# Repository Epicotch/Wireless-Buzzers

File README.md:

# Wireless Buzzers

### **NOTE: This thing was fairly slapdash and still has a few bugs. Only use this as a reference, not as a final product.**

3D printed parts: https://cad.onshape.com/documents/be3b52bcdf6f61d23120cde6/w/8980feb9664c58ae24ebe7fa/e/dfef3d1a1d06f241238ca187?renderMode=0&uiState=6670e02500c0bf5a21c60121

Shield: [![CC BY-NC 4.0][cc-by-nc-shield]][cc-by-nc]

This work is licensed under a
[Creative Commons Attribution-NonCommercial 4.0 International License][cc-by-nc].

[![CC BY-NC 4.0][cc-by-nc-image]][cc-by-nc]

[cc-by-nc]: https://creativecommons.org/licenses/by-nc/4.0/
[cc-by-nc-image]: https://licensebuttons.net/l/by-nc/4.0/88x31.png
[cc-by-nc-shield]: https://img.shields.io/badge/License-CC%20BY--NC%204.0-lightgrey.svg

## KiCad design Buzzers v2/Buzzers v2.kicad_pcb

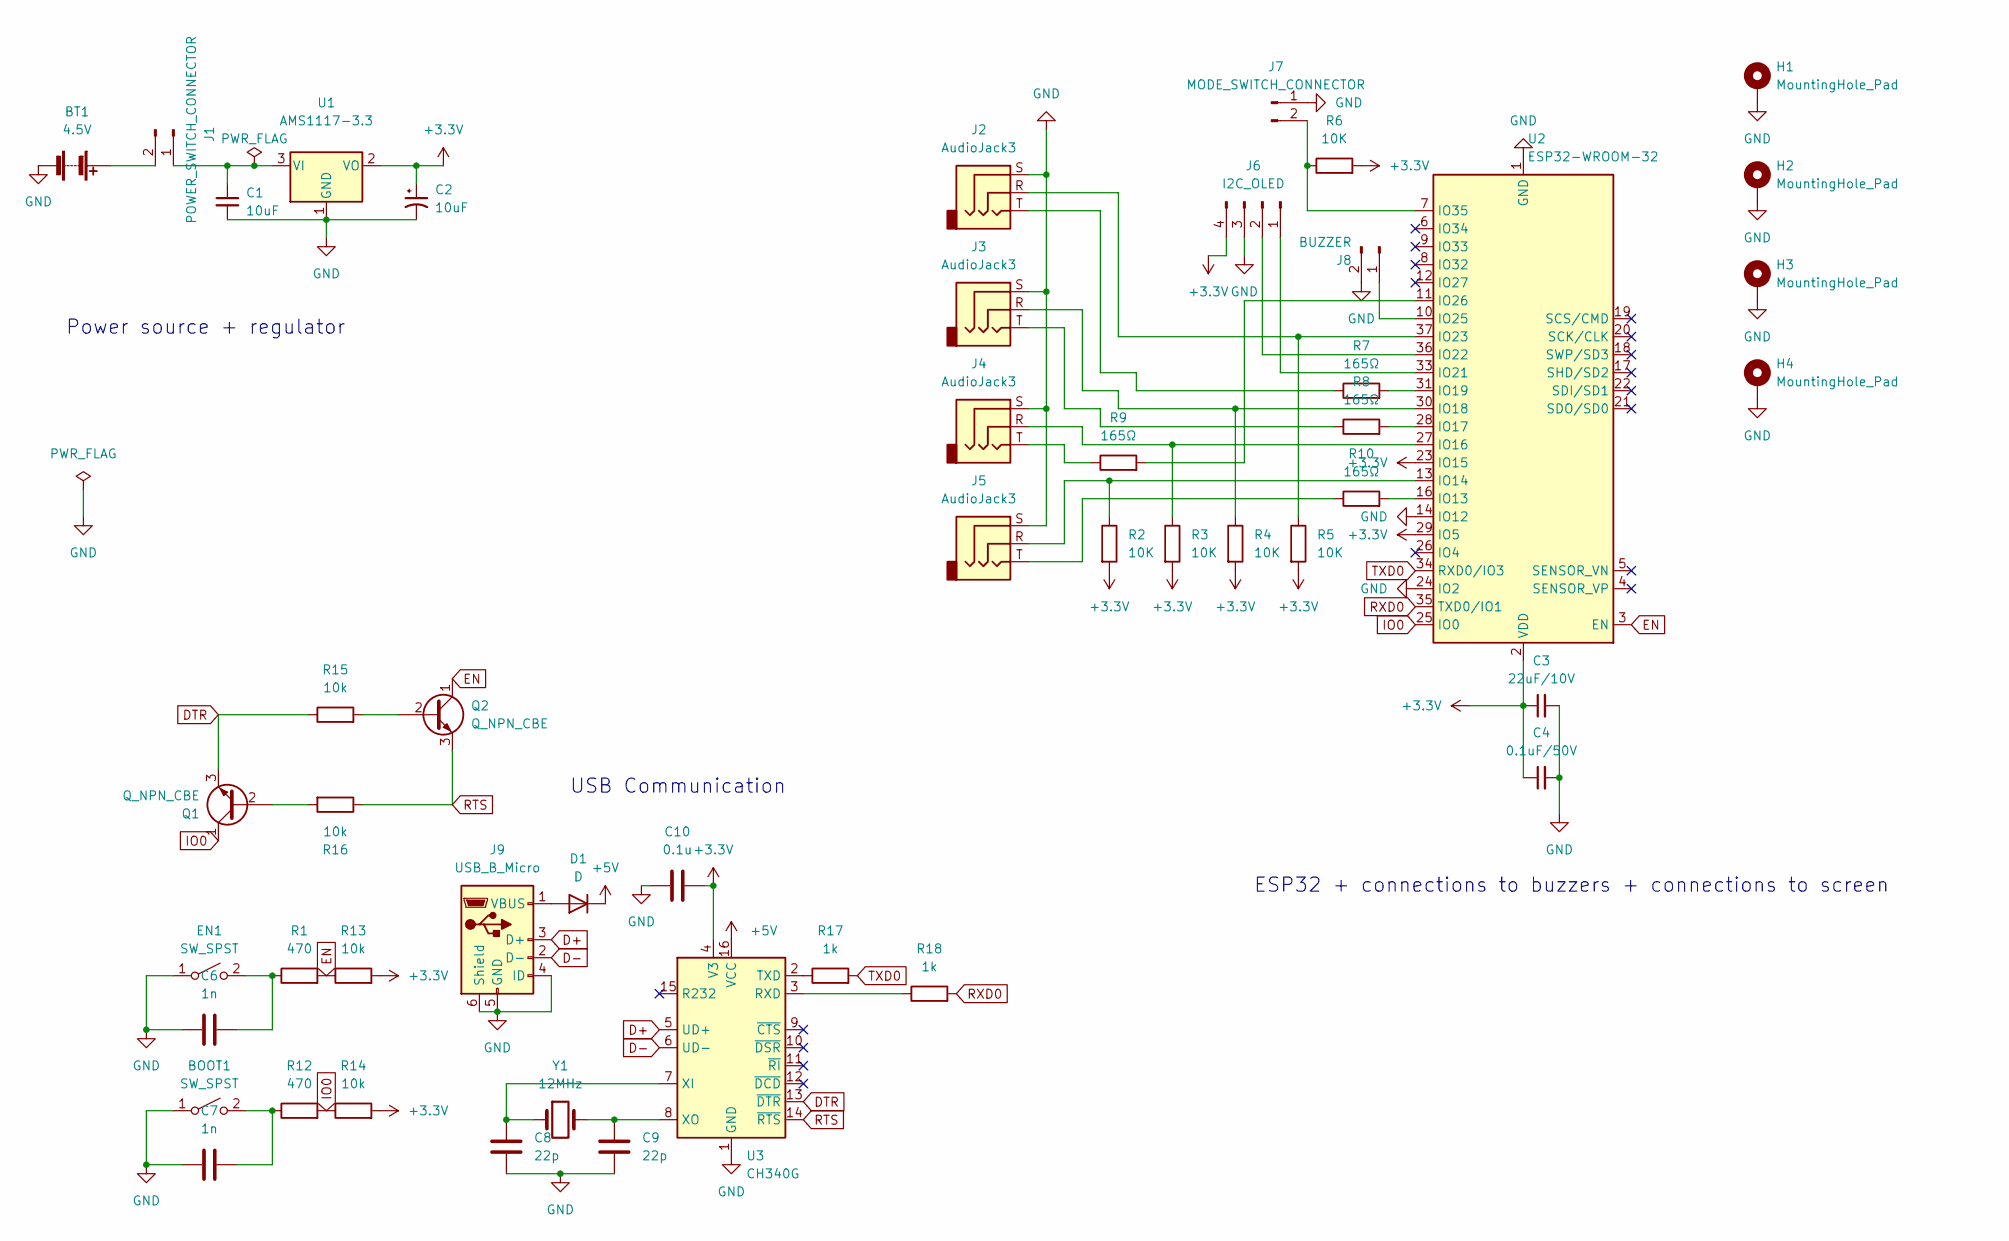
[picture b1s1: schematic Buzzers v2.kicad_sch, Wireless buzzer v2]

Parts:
BOOT1: SW_SPST; SW_PUSH_6mm_H5mm
BT1: 4.5V; BatteryHolder_TruPower_BH-331P_3xAA
C1: 10uF; C_1206_3216Metric
C2: 10uF; CP_EIA-3528-12_Kemet-T
C3: 22uF/10V; C_1206_3216Metric
C4: 0.1uF/50V; C_1206_3216Metric
C6, C7: 1n; C_1206_3216Metric
C8, C9: 22p; C_1206_3216Metric
C10: 0.1u; C_1206_3216Metric
D1: D; D_1206_3216Metric
EN1: SW_SPST; SW_PUSH_6mm_H5mm
H1, H2, H3, H4: MountingHole_Pad; MountingHole_3.5mm_Pad
J1: POWER_SWITCH_CONNECTOR; JST_XH_B2B-XH-A_1x02_P2.50mm_Vertical
J2, J3, J4, J5: AudioJack3; Jack_3.5mm_CUI_SJ1-3523N_Horizontal
J6: I2C_OLED; JST_XH_B4B-XH-A_1x04_P2.50mm_Vertical
J7: MODE_SWITCH_CONNECTOR; JST_XH_B2B-XH-A_1x02_P2.50mm_Vertical
J8: BUZZER; JST_XH_B2B-XH-A_1x02_P2.50mm_Vertical
J9: USB_B_Micro; USB_Micro-B_Amphenol_10103594-0001LF_Horizontal
Q1, Q2: Q_NPN_CBE; SOT-23
R1, R12: 470; R_1206_3216Metric
R2, R3, R4, R5, R6: 10K; R_1206_3216Metric
R7, R8, R9, R10: 165Ω; R_1206_3216Metric
R13, R14, R15, R16: 10k; R_1206_3216Metric
R17, R18: 1k; R_1206_3216Metric
U1: AMS1117-3.3; SOT-223-3_TabPin2
U2: ESP32-WROOM-32
U3: CH340G; SOIC-16_3.9x9.9mm_P1.27mm
Y1: 12MHz; Crystal_HC49-U_Vertical

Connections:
+3.3V: C2.1, C3.1, C4.1, C10.2, J6.4, R2.2, R3.2, R4.2, R5.2, R6.2, R13.2, R14.2, U1.2 (VO), U2.2 (VDD), U2.23 (IO15), U2.29 (IO5), U3.4 (V3)
+5V: D1.1 (K), U3.16 (VCC)
D+: J9.3 (D+), U3.5 (UD+)
D-: J9.2 (D-), U3.6 (UD-)
DTR: Q1.3 (E), R15.1, U3.13 (~DTR)
EN: Q2.1 (C), R1.2, R13.1, U2.3 (EN)
GND: BOOT1.1 (A), BT1.2 (-), C1.2, C2.2, C3.2, C4.2, C6.1, C7.1, C8.2, C9.2, C10.1, EN1.1 (A), H1.1, H2.1, H3.1, H4.1, J2.S, J3.S, J4.S, J5.S, J6.3, J7.1, J8.2, J9.4 (ID), J9.5 (GND), J9.6 (Shield), U1.1 (GND), U2.1 (GND), U2.14 (IO12), U2.15 (GND), U2.24 (IO2), U2.38 (GND), U2.39 (GND), U3.1 (GND)
IO0: Q1.1 (C), R12.2, R14.1, U2.25 (IO0)
unnamed: BT1.1 (+), J1.2
unnamed: C1.1, J1.1, U1.3 (VI)
unnamed: C6.2, EN1.2 (B), R1.1
unnamed: BOOT1.2 (B), C7.2, R12.1
unnamed: C8.1, U3.7 (XI), Y1.1
unnamed: C9.1, U3.8 (XO), Y1.2
unnamed: D1.2 (A), J9.1 (VBUS)
unnamed: J2.R, R5.1, U2.37 (IO23)
unnamed: J2.T, R7.1
unnamed: J3.R, R4.1, U2.30 (IO18)
unnamed: J3.T, R8.1
unnamed: J4.R, R3.1, U2.27 (IO16)
unnamed: J4.T, R9.1
unnamed: J5.R, R2.1, U2.13 (IO14)
unnamed: J5.T, R10.1
unnamed: J6.1, U2.33 (IO21)
unnamed: J6.2, U2.36 (IO22)
unnamed: J7.2, R6.1, U2.7 (IO35)
unnamed: J8.1, U2.10 (IO25)
unnamed: Q1.2 (B), R16.2
unnamed: Q2.2 (B), R15.2
unnamed: R7.2, U2.31 (IO19)
unnamed: R8.2, U2.28 (IO17)
unnamed: R10.2, U2.16 (IO13)
unnamed: R17.1, U3.2 (TXD)
unnamed: R18.1, U3.3 (RXD)
unnamed: R9.2, U2.11 (IO26)
RTS: Q2.3 (E), R16.1, U3.14 (~RTS)
RXD0: R18.2, U2.35 (TXD0/IO1)
TXD0: R17.2, U2.34 (RXD0/IO3)

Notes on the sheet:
ESP32 + connections to buzzers + connections to screen
USB Communication
Power source + regulator

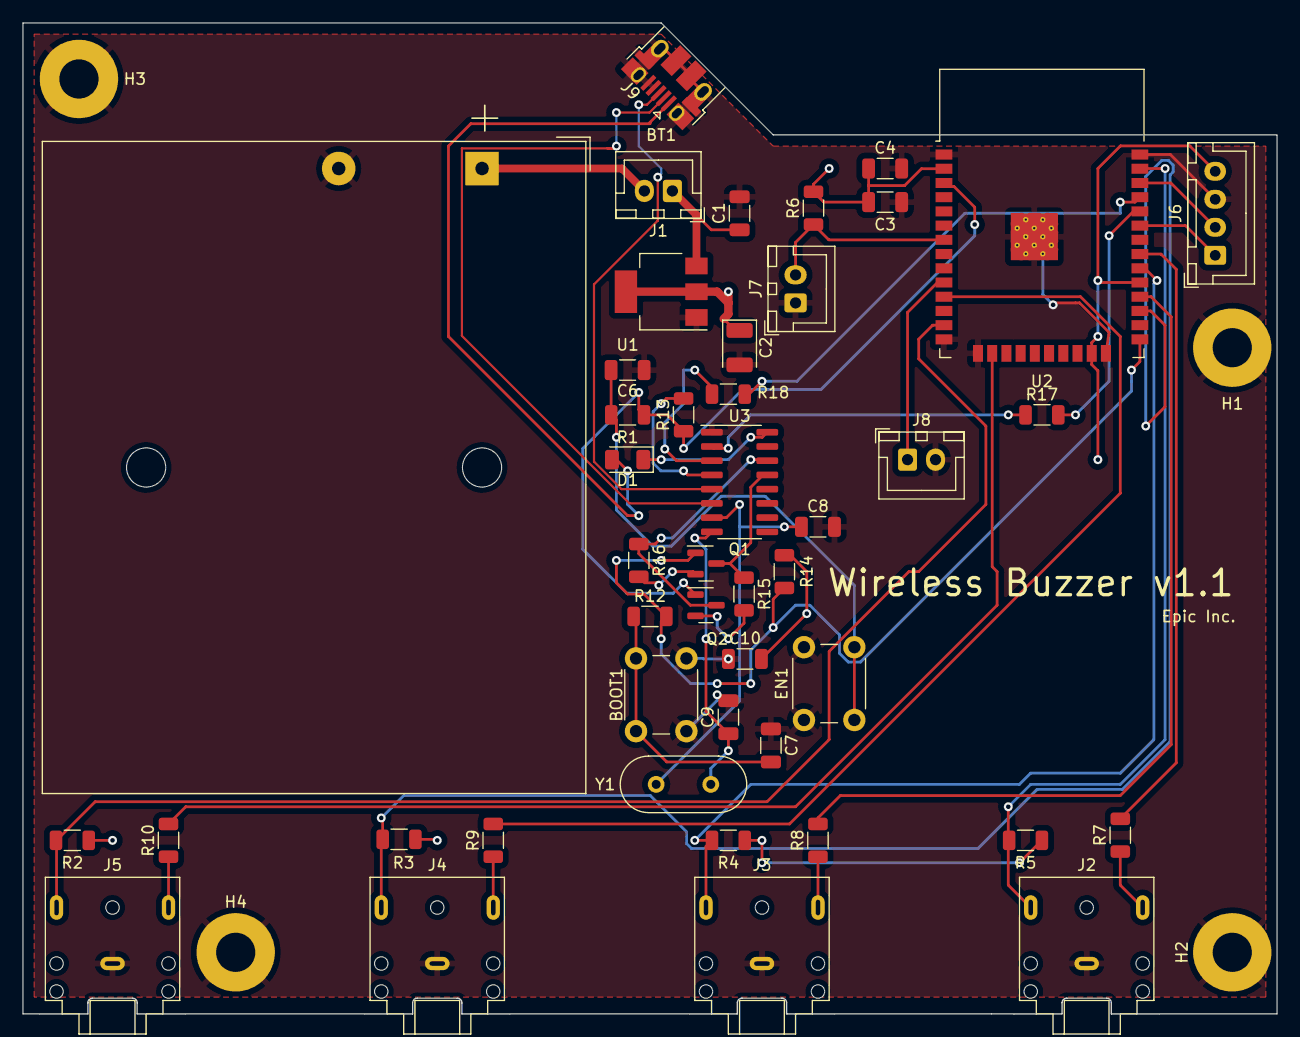
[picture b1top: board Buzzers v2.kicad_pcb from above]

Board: 2 copper layers, 112.0 x 88.5 mm, 49 parts (0 on the bottom side), 38 nets.

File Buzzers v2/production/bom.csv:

Designator,Footprint,Quantity,Value,LCSC Part #
"BOOT1, EN1",SW_PUSH_6mm_H5mm,2,SW_SPST,
BT1,BatteryHolder_TruPower_BH-331P_3xAA,1,4.5V,
C1,1206,1,10uF,
C10,1206,1,0.1u,
C2,CP_EIA-3528-12_Kemet-T,1,10uF,
C3,1206,1,22uF/10V,
C4,1206,1,0.1uF/50V,
"C6, C7",1206,2,1n,
"C8, C9",1206,2,22p,
D1,1206,1,D,
"H1, H2, H3, H4",MountingHole_3.5mm_Pad,4,MountingHole_Pad,
J1,JST_XH_B2B-XH-A_1x02_P2.50mm_Vertical,1,POWER_SWITCH_CONNECTOR,
"J2, J3, J4, J5",Jack_3.5mm_CUI_SJ1-3523N_Horizontal,4,AudioJack3,
J6,JST_XH_B4B-XH-A_1x04_P2.50mm_Vertical,1,I2C_OLED,
J7,JST_XH_B2B-XH-A_1x02_P2.50mm_Vertical,1,MODE_SWITCH_CONNECTOR,
J8,JST_XH_B2B-XH-A_1x02_P2.50mm_Vertical,1,BUZZER,
J9,USB_Micro-B_Amphenol_10103594-0001LF_Horizontal,1,USB_B_Micro,
"Q1, Q2",SOT-23,2,Q_NPN_CBE,
"R1, R12",1206,2,470,
"R10, R7, R8, R9",1206,4,165Ω,
"R13, R14, R15, R16, R2, R3, R4, R5, R6",1206,9,10k,
"R17, R18",1206,2,1k,
U1,SOT-223-3_TabPin2,1,AMS1117-3.3,
U2,ESP32-WROOM-32,1,ESP32-WROOM-32,
U3,SOIC-16_3.9x9.9mm_P1.27mm,1,CH340G,
Y1,Crystal_HC49-U_Vertical,1,12MHz,

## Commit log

2023-06-28 Starting things (mosty copied from tutorial)
2023-06-28 Rewriting most of it - created console side discovery connection, screen not implemented.
2023-06-28 Added buzzer discovery logic
2023-06-28 Added buzzing logic on the buzzer side
2023-06-28 Polishing buzzer logic
2023-06-28 Oops forgot to wrap it all in a check
2023-07-05 Theoretically finished the code (finished console logic)
2023-08-08 Added SSD 1306 display output
2023-09-02 Basically made the rest of the code
2023-09-02 Added 6 buzzer functionaliy
2023-11-14 Fixed crashing when trying to reset and buzz at the same time
2024-06-18 Create LICENSE
2024-06-18 Update LICENSE
2024-06-18 PCB Upload stuff
    aaaaa this is a mess
